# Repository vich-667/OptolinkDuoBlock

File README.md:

# Optolink Duo Block

This project was created to have local access to the viessmann heating system to monitor and control and have the vitoconnect still working.
In [OpenV Wiki](https://github.com/openv/openv) and it's issue section can be found a lot of information and links to other interesting Projects.
But all of them either only monitor the communication between the heating system and the vitoconnect or the directly communicate with the heating system.
Therefore, this project was started to control the connection of the vitoconnect from the monitoring pc.

The basic idea of this project was taken from [USB_Duo-Sniffer](https://github.com/openv/openv/wiki/Bauanleitung-USB_Duo-Sniffer).
I extended the circuit to be able to block the vitoconnect to be able to send read or write commands directly to the heating system.

Finally, the heatpump should be integrated into my [OpenHAB](https://www.openhab.org/) installation to monitor the status and
control it depending on PV power and weather situation. Due to the reason I'm not very familiar with Java (and the long delay of PR reviews) I wrote the
Software with Python and reused a simple HTTP Server from another Project to integrate it into OpenHABs via the http plugin. So this Project can be also
reused in other context.

## Project

| Folder     | Content                                                                                                                           |
|------------|-----------------------------------------------------------------------------------------------------------------------------------|
| Datasheet  | Datasheets of used components                                                                                                     |
| PCB        | Schematic and PCP design. Created with [KiCad](https://www.kicad.org/)                                                            |
| Pictures   | Pictures of the Optolink Duo Block                                                                                                |
| Simulation | Electrical Simulation with [LTSpice](https://www.analog.com/en/design-center/design-tools-and-calculators/ltspice-simulator.html) |
| Software   | Software to monitor and read/write written in Python.                                                                             |

## Hardware

The schematic from [USB_Duo-Sniffer](https://github.com/openv/openv/wiki/Bauanleitung-USB_Duo-Sniffer)
was reused and extended in a way that with the DTR Pin of the sniffer PC the Tx as well the Rx from the Vitoconnect can be blocked. In block mode 
read and write messages can be sent directly to the heating system. In unblock mode the vitoconnect can communicate and the communication can be monitored.

The IR PCB was created in a similar way you can find it in [OpenV Wiki](https://github.com/openv/openv)
as well. To fit it exact inside the cover, I simply put some tape around it and filled up the backside with
hot glue, that it has nearby the same size as the original. 

The circuit was soldered with TH components. And placed into an additional box. The advantage of this hardware solution over a proxy solution is that the vitoconnect can work
as long the pc is not connected or the DTR pin is low.

# Software
The `vito_monitor_ctrl` is the basic lib (it can be reused in other applications or projects) what provides the `VitocalHandler` class. This class factor the whole thing and
provides methods to read and write data points.

Basically there is the `VitoDatahandler` Interface with its two implementation, for monitoring the vitoconnect and the direct read / write access. To not direct deepened on any
hardware there is the `OptolinkMAC` to abstract them. An implementation for the **OptolinkDuoBlock** as well as a Dummy for testing without hardware exists. Also a implementation
for the Proxy solution was created, but never tested or used.

## Configuration
Data point to be read and write need to be configured either statically via `value_config.py` or you can set the dict during runtime. This dict contains the data point names as
key and a parameter dict with fixed names.
 
`"Aussentemperatur": { "address": 0x1234, "unit": "UT", "access": 1 , "description": "anyting, currently unused", "data_bytes": 4 }`

| Key         | Info                                                                             |
|-------------|----------------------------------------------------------------------------------|
| address     | Address of data point                                                            |
| unit        | Unit to convert data, see `vito_data_handler.py`                                 |
| data_bytes  | Number of bytes to read / write independent from unit                            |
| access      | Access type: MONITOR = 0x01, READOUT = 0x02, WRITE = 0x04 or any and combination |
| description | Any description, currently not used                                              |

## Applications

- `cmd_line_main.py`: This application provides a simple shell for testing
  - press Enter to print out the current values
  - `w <data_point_name> <value>` to write a data point
  - `exit` to close

- `http_server_main.py`: http server to be accessed from any other tools
  - it simply can be tested with `curl localhost:8006 | jq -C`
  - GET `http://localhost:8006` or `http://localhost:8006/getstatus/` a json object with all current values and system status is provided
  - POST `http://localhost:8006/set/vito/<data_point_name>` to write the data, the value need to be provided as a plain test
  - POST `http://localhost:8006/set/vito/configuration` to set the config. It needs to be provided as a json object

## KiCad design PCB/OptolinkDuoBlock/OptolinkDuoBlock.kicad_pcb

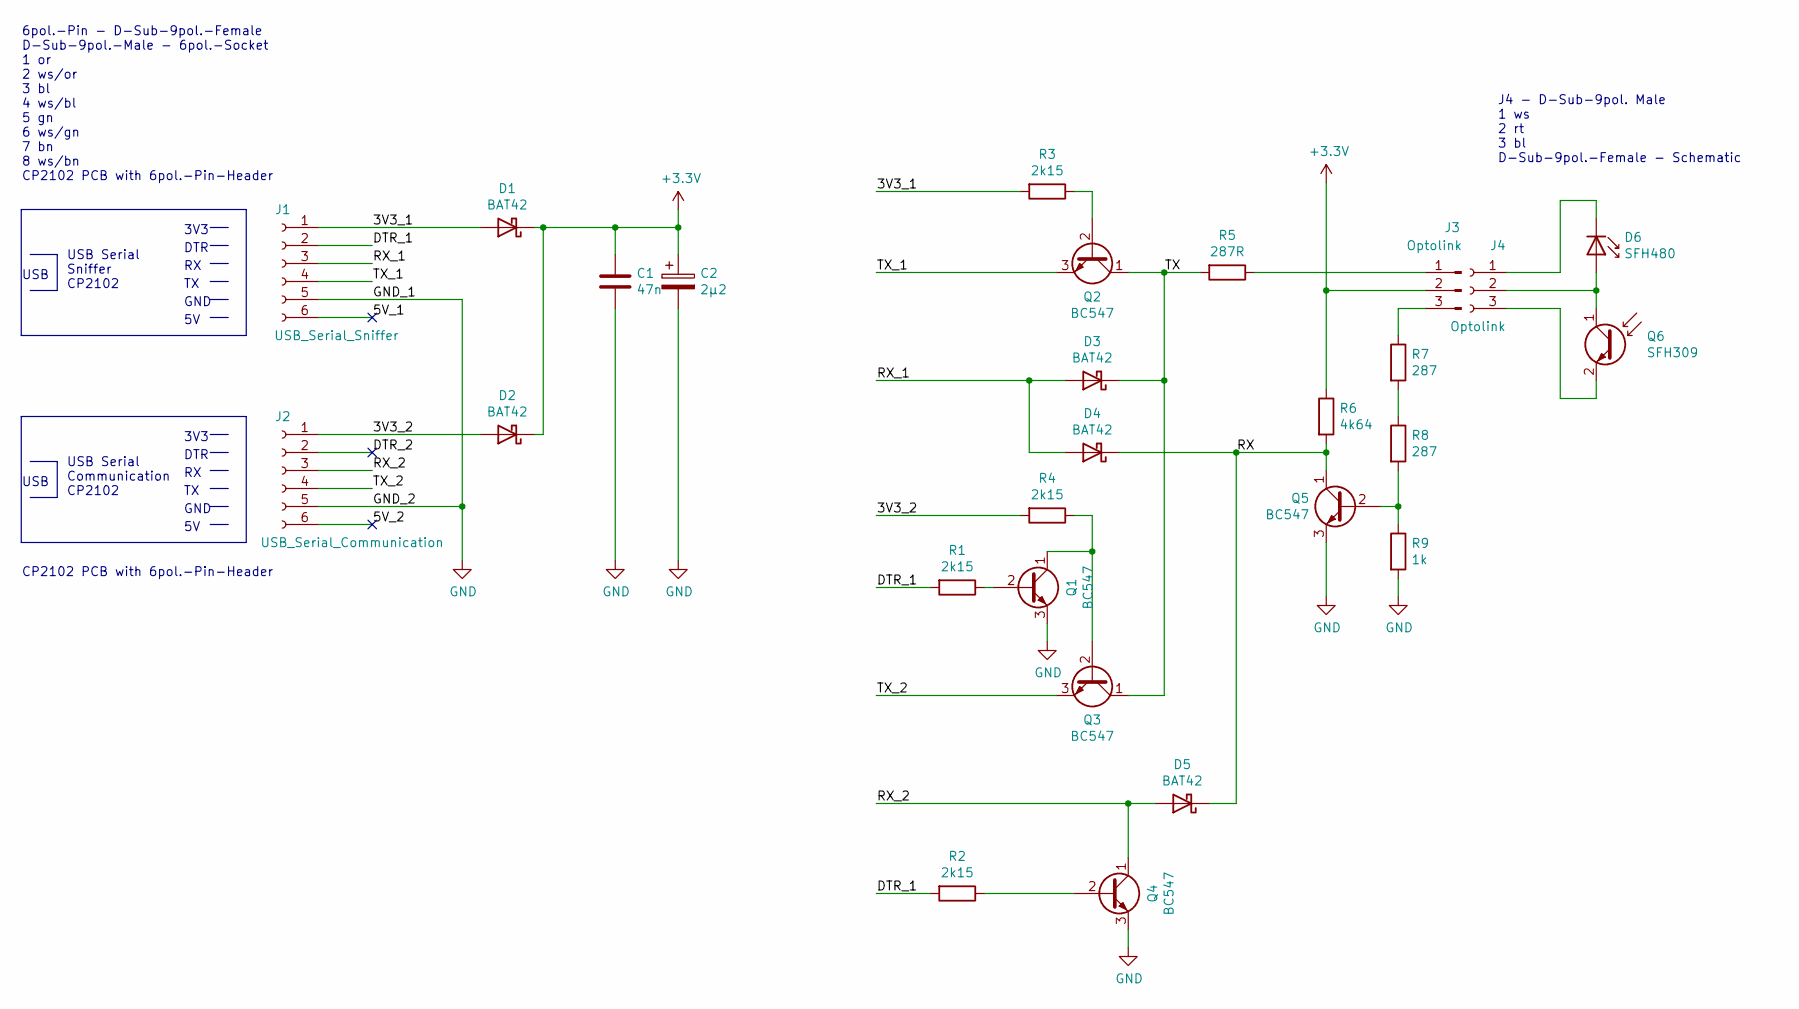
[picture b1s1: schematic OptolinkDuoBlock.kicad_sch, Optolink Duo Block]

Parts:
C1: 47n; C_Disc_D7.5mm_W5.0mm_P7.50mm
C2: 2µ2; CP_Radial_D5.0mm_P2.50mm
D1, D2, D3, D4, D5: BAT42; D_DO-35_SOD27_P7.62mm_Horizontal
D6: SFH480; TO-18-2_Window
J1: USB_Serial_Sniffer; PinSocket_1x06_P2.54mm_Vertical
J2: USB_Serial_Communication; PinSocket_1x06_P2.54mm_Vertical
J3: Optolink; PinHeader_1x03_P2.54mm_Vertical
J4: Optolink; PinSocket_1x03_P2.54mm_Vertical
Q1, Q2, Q3, Q4, Q5: BC547; TO-92L_Inline_Wide
Q6: SFH309; LED_D3.0mm_Clear
R1, R2, R3, R4: 2k15; R_Axial_DIN0207_L6.3mm_D2.5mm_P10.16mm_Horizontal
R5: 287R; R_Axial_DIN0207_L6.3mm_D2.5mm_P10.16mm_Horizontal
R6: 4k64; R_Axial_DIN0207_L6.3mm_D2.5mm_P10.16mm_Horizontal
R7, R8: 287; R_Axial_DIN0207_L6.3mm_D2.5mm_P10.16mm_Horizontal
R9: 1k; R_Axial_DIN0207_L6.3mm_D2.5mm_P10.16mm_Horizontal

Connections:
+3V3: C1.1, C2.1, D1.1 (K), D2.1 (K), J3.2, R6.1
/3V3_1: D1.2 (A), J1.1, R3.2
/3V3_2: D2.2 (A), J2.1, R4.2
/5V_1: J1.6
/5V_2: J2.6
/DTR_1: J1.2, R1.2, R2.2
/DTR_2: J2.2
/RX: D4.1 (K), D5.1 (K), Q5.1 (C), R6.2
/RX_1: D3.2 (A), D4.2 (A), J1.3
/RX_2: D5.2 (A), J2.3, Q4.1 (C)
/TX: D3.1 (K), Q2.1 (C), Q3.1 (C), R5.2
/TX_1: J1.4, Q2.3 (E)
/TX_2: J2.4, Q3.3 (E)
GND: C1.2, C2.2, J1.5, J2.5, Q1.3 (E), Q4.3 (E), Q5.3 (E), R9.2
unnamed: D6.2 (A), J4.2, Q6.1 (C)
unnamed: D6.1 (K), J4.1
unnamed: J3.1, R5.1
unnamed: J3.3, R7.1
unnamed: J4.3, Q6.2 (E)
unnamed: Q1.2 (B), R1.1
unnamed: Q1.1 (C), Q3.2 (B), R4.1
unnamed: Q2.2 (B), R3.1
unnamed: Q4.2 (B), R2.1
unnamed: Q5.2 (B), R8.2, R9.1
unnamed: R7.2, R8.1

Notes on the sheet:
J4 - D-Sub-9pol. Male 1 ws 2 rt 3 bl D-Sub-9pol.-Female - Schematic
USB
DTR
GND
3V3
USB Serial Communication CP2102
USB Serial Sniffer CP2102
CP2102 PCB with 6pol.-Pin-Header
6pol.-Pin - D-Sub-9pol.-Female D-Sub-9pol.-Male - 6pol.-Socket 1 or 2 ws/or 3 bl 4 ws/bl 5 gn 6 ws/gn 7 bn 8 ws/bn CP2102 PCB with 6pol.-Pin-Header

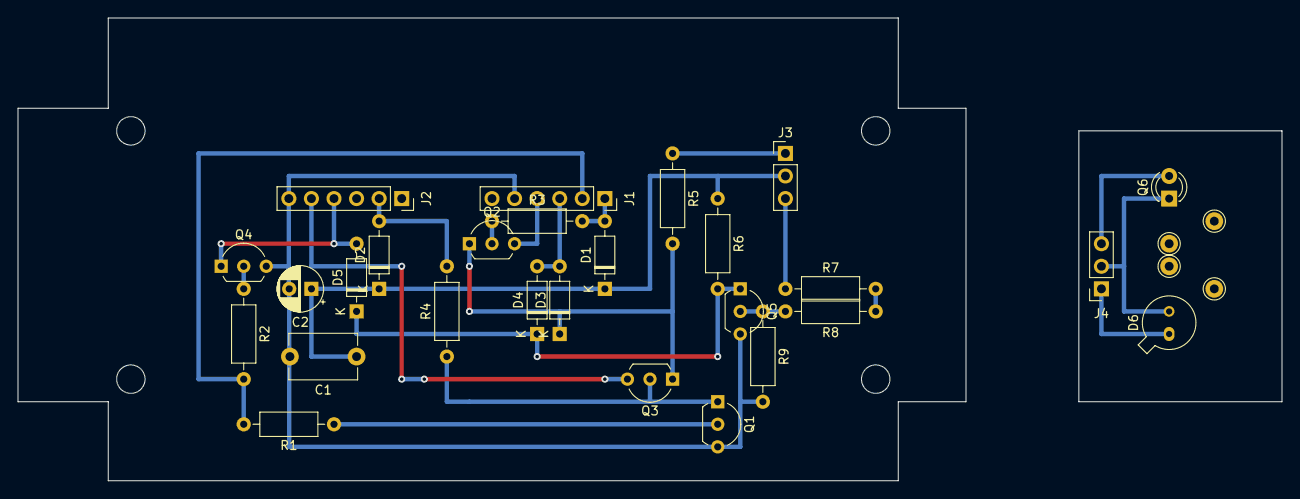
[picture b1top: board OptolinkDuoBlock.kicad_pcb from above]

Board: 2 copper layers, 142.2 x 52.1 mm, 27 parts (0 on the bottom side), 22 nets.

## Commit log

2023-04-15 V1.0
2023-05-13 fixed write len config
2023-05-20 add V1.1.0
2024-08-20 db_logging
